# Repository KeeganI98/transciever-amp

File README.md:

# transciever-amp

Amplifier circuit to be used with LILYGO T-Beam Supreme.

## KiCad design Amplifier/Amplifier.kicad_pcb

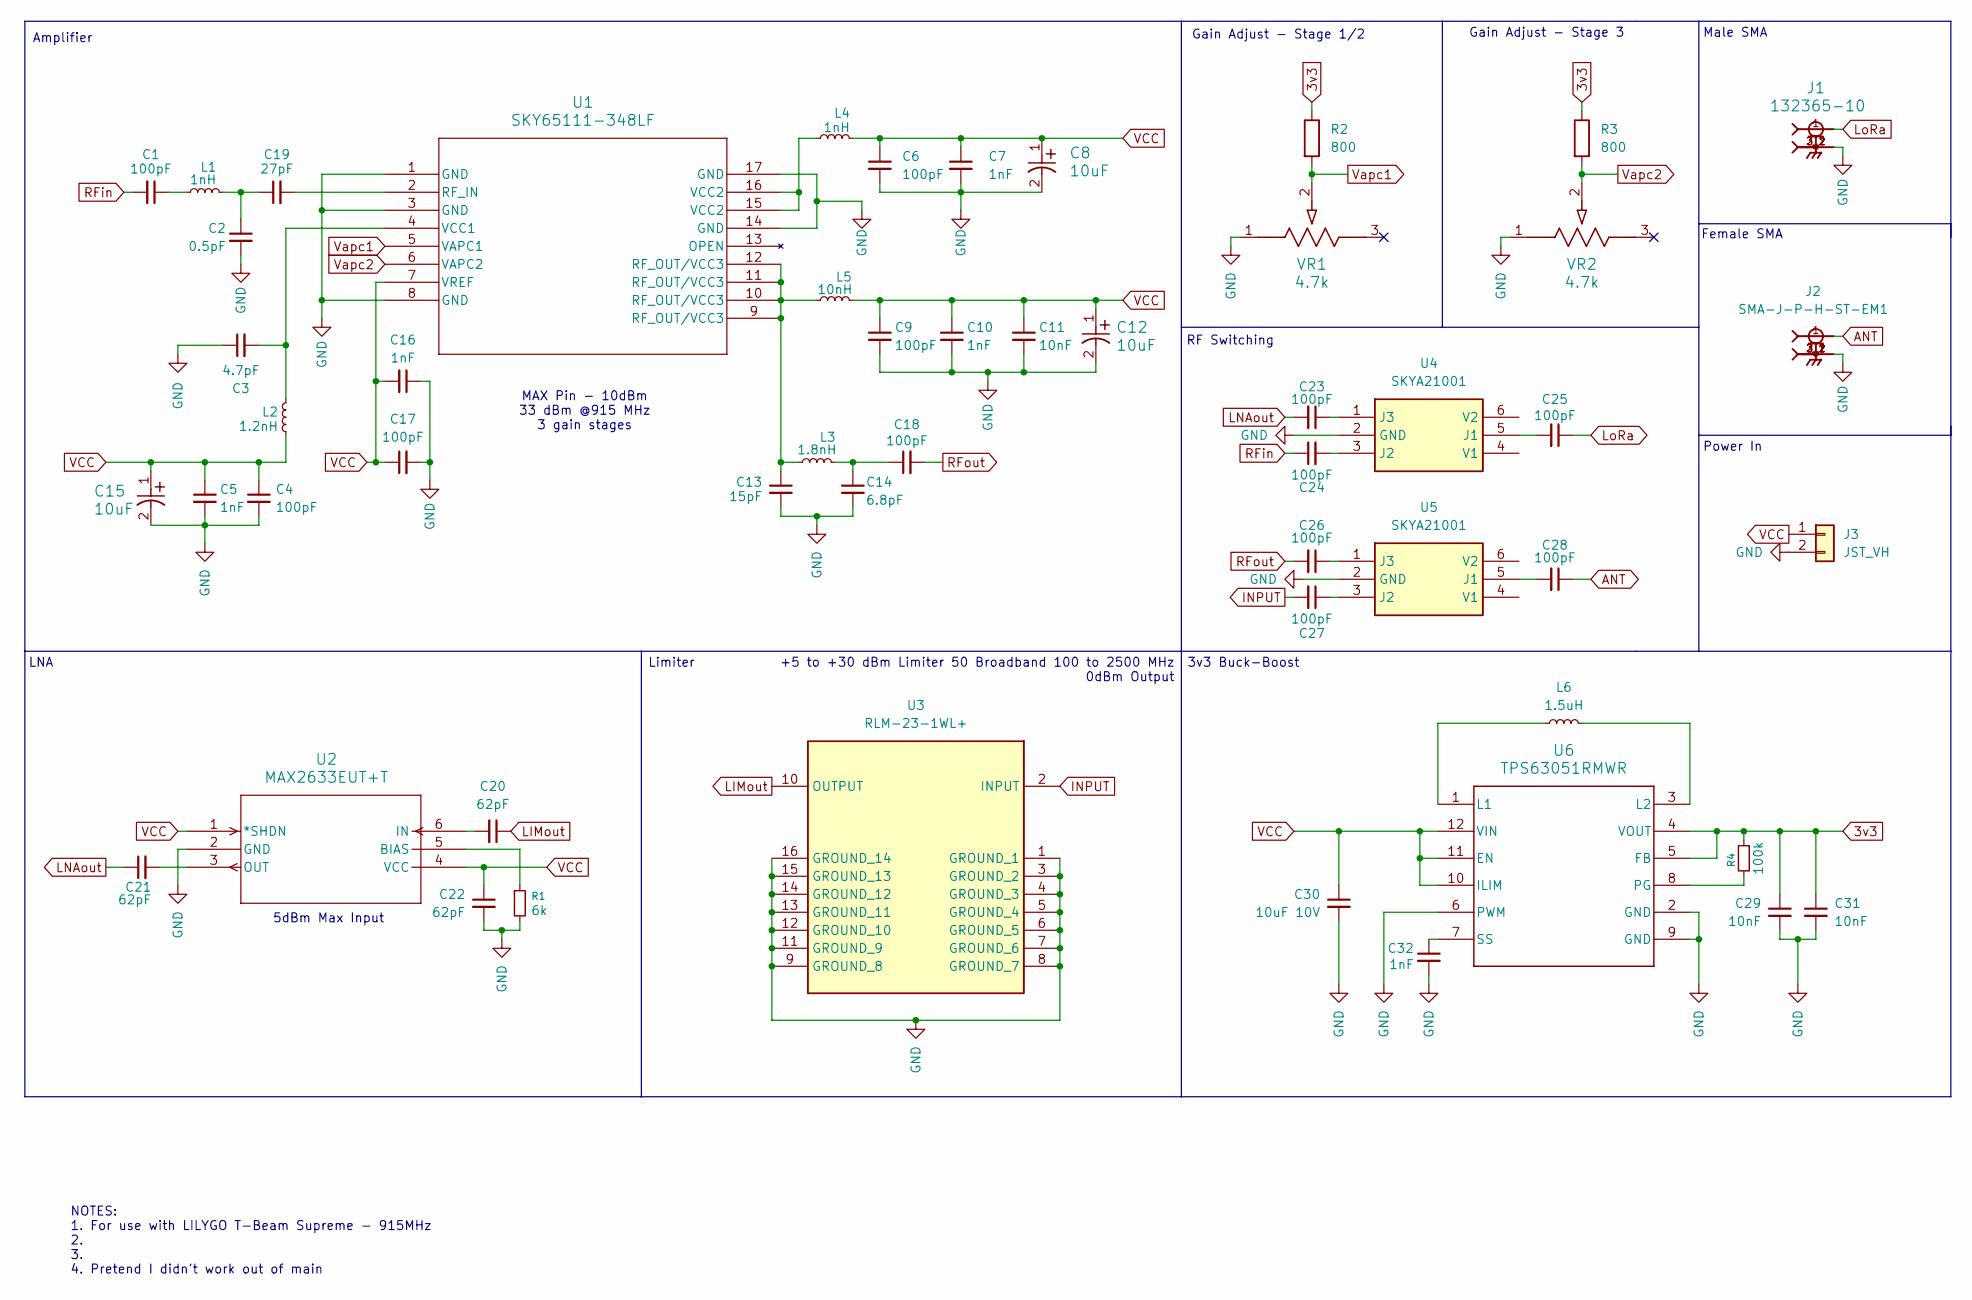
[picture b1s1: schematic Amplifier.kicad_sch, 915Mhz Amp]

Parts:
C1, C4, C6, C9, C17, C18, C23, C24, C25, C26, C27, C28: 100pF; C_0402_1005Metric; LCSCPart C3892243
C2: 0.5pF; C_0402_1005Metric; LCSCPart C76912
C3: 4.7pF; C_0402_1005Metric; LCSCPart C161327
C5, C7, C10, C16, C32: 1nF; C_0402_1005Metric; LCSCPart C77018
C8, C12, C15: 10uF; TAJA_AVX; LCSCPart C99352
C11: 10nF; C_0402_1005Metric; LCSCPart C77013
C13: 15pF; C_0402_1005Metric; LCSCPart C441742
C14: 6.8pF; C_0402_1005Metric; LCSCPart C2169817
C19: 27pF; C_0402_1005Metric; LCSCPart C88883
C20, C21, C22: 62pF; C_0603_1608Metric; LCSCPart C2171209
C29, C31: 10nF; C_0603_1608Metric; LCSCPart C77041
C30: 10uF 10V; C_0603_1608Metric; LCSCPart C2167467
J1: 132365-10; CONN_132365-10_AMP; LCSCPart C3172997
J2: SMA-J-P-H-ST-EM1; SAMTEC_SMA-J-P-H-ST-EM1; LCSCPart C5199907
J3: JST_VH; JST_VH_B2P-VH-FB-B_1x02_P3.96mm_Vertical
L1, L4: 1nH; LQG15WH0N7B02D; LCSCPart C3910364
L2: 1.2nH; LQG15WH0N7B02D; LCSCPart C488336
L3: 1.8nH; LQG15WH0N7B02D; LCSCPart C3911287
L5: 10nH; L_0603_1608Metric; LCSCPart C3220902
L6: 1.5uH; L_1008_2520Metric; LCSCPart C98034
R1: 6k; R_0402_1005Metric
R2, R3: 800; R_0402_1005Metric
R4: 100k; R_0603_1608Metric; LCSCPart C14675
U1: SKY65111-348LF; QFN_SKY65111_SKY; LCSCPart C2654167
U2: MAX2633EUT+T; 21-0058I_MXM; JLCPart C490978
U3: RLM-23-1WL+; RLM231WL; LCSCPart C7288002
U4, U5: SKYA21001; SOT65P220X110-6N; LCSCPart C2151939
U6: TPS63051RMWR; RMW0012A; LCSCPart C139412
VR1, VR2: 4.7k; POT_3386G; LCSCPart C6410772

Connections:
3v3: C29.1, C31.1, R2.1, R3.1, R4.1, U6.4 (VOUT), U6.5 (FB)
ANT: C28.1, J2.1
GND: C2.2, C3.1, C4.2, C5.2, C6.2, C7.2, C8.2, C9.2, C10.2, C11.2, C12.2, C13.2, C14.2, C15.2, C16.1, C17.2, C22.2, C29.2, C30.2, C31.2, C32.2, J1.2, J1.2_2, J1.3, J1.3_1, J1.3_2, J1.4, J1.5, J2.2_1, J2.2_2, J2.3_1, J2.3_2, J3.2, R1.2, U1.1 (GND), U1.3 (GND), U1.8 (GND), U1.14 (GND), U1.17 (GND), U2.2 (GND), U3.1 (GROUND_1), U3.3 (GROUND_2), U3.4 (GROUND_3), U3.5 (GROUND_4), U3.6 (GROUND_5), U3.7 (GROUND_6), U3.8 (GROUND_7), U3.9 (GROUND_8), U3.11 (GROUND_9), U3.12 (GROUND_10), U3.13 (GROUND_11), U3.14 (GROUND_12), U3.15 (GROUND_13), U3.16 (GROUND_14), U4.2 (GND), U5.2 (GND), U6.2 (GND), U6.6 (PWM), U6.9 (GND), VR1.1, VR2.1
INPUT: C27.2, U3.2 (INPUT)
LIMout: C20.1, U3.10 (OUTPUT)
LNAout: C21.1, C23.2
LoRa: C25.1, J1.1
unnamed: C1.1, L1.1
unnamed: C13.1, L3.1, L5.1, U1.9 (RF_OUT/VCC3), U1.10 (RF_OUT/VCC3), U1.11 (RF_OUT/VCC3), U1.12 (RF_OUT/VCC3)
unnamed: C14.1, C18.1, L3.2
unnamed: C2.1, C19.1, L1.2
unnamed: L4.1, U1.15 (VCC2), U1.16 (VCC2)
unnamed: C19.2, U1.2 (RF_IN)
unnamed: C3.2, L2.2, U1.4 (VCC1)
unnamed: R1.1, U2.5 (BIAS)
unnamed: C20.2, U2.6 (IN)
unnamed: C21.2, U2.3 (OUT)
unnamed: C25.2, U4.5 (J1)
unnamed: C24.2, U4.3 (J2)
unnamed: C23.1, U4.1 (J3)
unnamed: C28.2, U5.5 (J1)
unnamed: C27.1, U5.3 (J2)
unnamed: C26.1, U5.1 (J3)
unnamed: L6.1, U6.1 (L1)
unnamed: L6.2, U6.3 (L2)
unnamed: R4.2, U6.8 (PG)
unnamed: C32.1, U6.7 (SS)
RFin: C1.2, C24.1
RFout: C18.2, C26.2
VCC: C4.1, C5.1, C6.1, C7.1, C8.1, C9.1, C10.1, C11.1, C12.1, C15.1, C16.2, C17.1, C22.1, C30.1, J3.1, L2.1, L4.2, L5.2, U1.7 (VREF), U2.1 (*SHDN), U2.4 (VCC), U6.10 (ILIM), U6.11 (EN), U6.12 (VIN)
Vapc1: R2.2, U1.5 (VAPC1), VR1.2
Vapc2: R3.2, U1.6 (VAPC2), VR2.2

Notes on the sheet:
Amplifier
MAX Pin - 10dBm 33 dBm @915 MHz 3 gain stages
Male SMA
RF Switching
5dBm Max Input
Power In
Gain Adjust - Stage 1/2
+5 to +30 dBm Limiter 50 Broadband 100 to 2500 MHz 0dBm Output
Gain Adjust - Stage 3
LNA
Limiter
Female SMA
3v3 Buck-Boost
NOTES: 1. For use with LILYGO T-Beam Supreme - 915MHz 2. 3. 4. Pretend I didn't work out of main

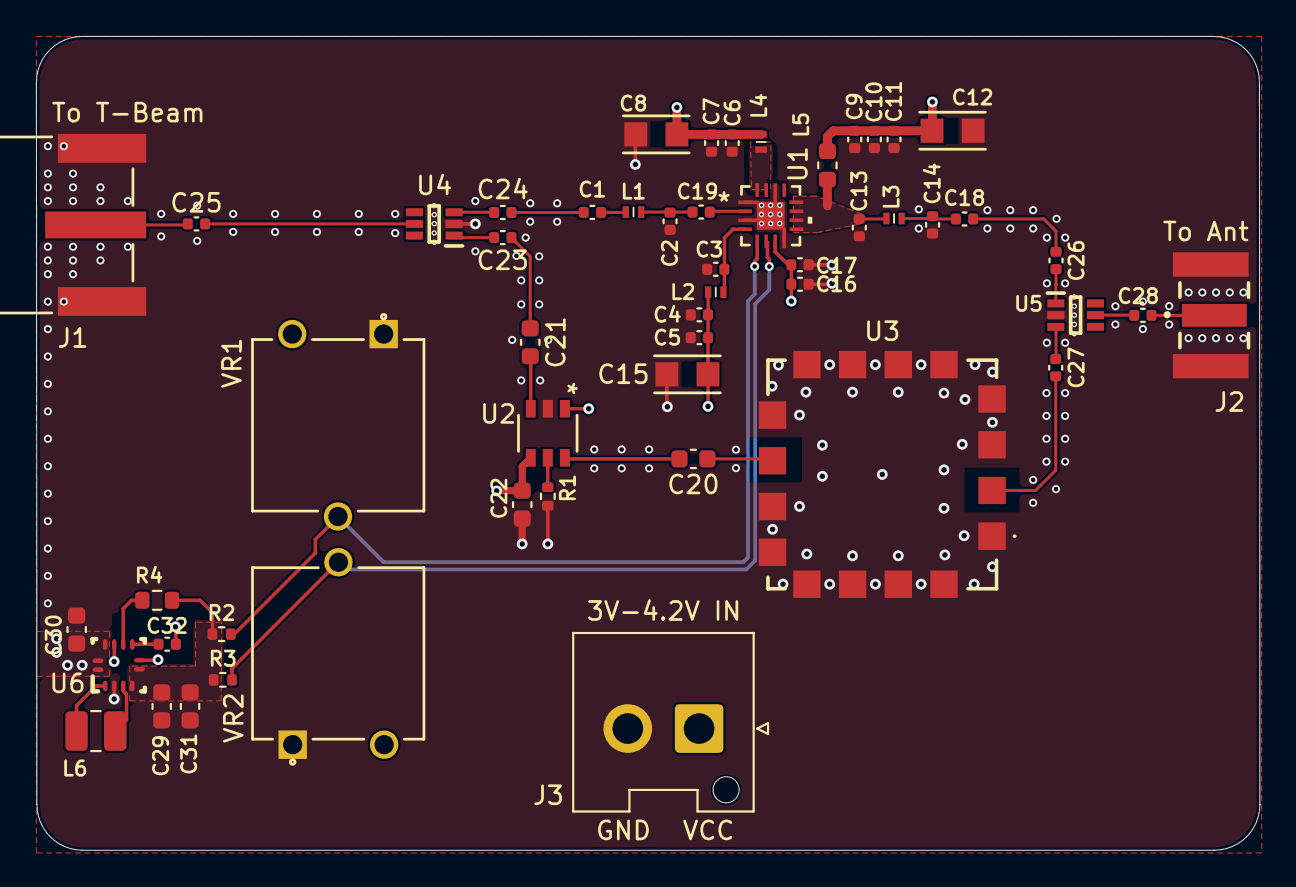
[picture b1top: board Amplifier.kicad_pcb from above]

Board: 4 copper layers, 68.0 x 45.2 mm, 53 parts (0 on the bottom side), 32 nets.
